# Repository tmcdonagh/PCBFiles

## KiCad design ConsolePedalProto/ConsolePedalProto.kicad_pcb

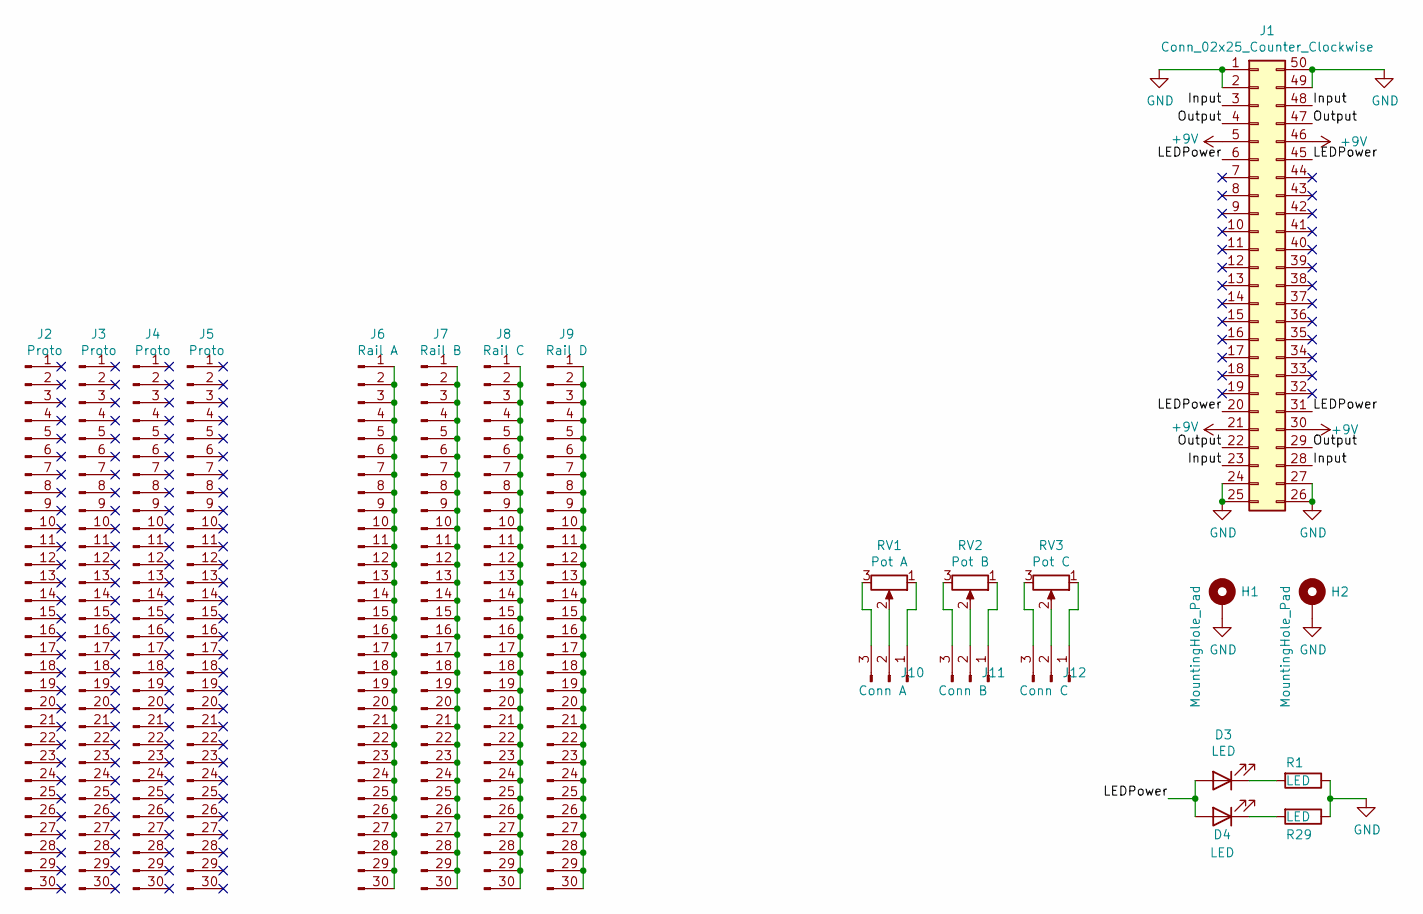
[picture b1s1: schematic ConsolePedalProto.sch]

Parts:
D3, D4: LED; LED_D5.0mm
H1, H2: MountingHole_Pad; MountingHole_2.5mm_Pad
J1: Conn_02x25_Counter_Clockwise; N64-Connector
J2, J3, J4, J5: Proto; PinSocket_1x30_P2.54mm_Vertical
J6: Rail A; Rail
J7: Rail B; Rail
J8: Rail C; Rail
J9: Rail D; Rail
J10: Conn A; PinSocket_1x03_P2.54mm_Vertical
J11: Conn B; PinSocket_1x03_P2.54mm_Vertical
J12: Conn C; PinSocket_1x03_P2.54mm_Vertical
R1, R29: LED; R_Axial_DIN0207_L6.3mm_D2.5mm_P10.16mm_Horizontal
RV1: Pot A; Potentiometer_Bourns_PTV09A-1_Single_Vertical
RV2: Pot B; Potentiometer_Bourns_PTV09A-1_Single_Vertical
RV3: Pot C; Potentiometer_Bourns_PTV09A-1_Single_Vertical

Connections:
+9V: J1.5, J1.21, J1.30, J1.46
/Input: J1.3, J1.23, J1.28, J1.48
/LEDPower: D3.2 (A), D4.2 (A), J1.6, J1.20, J1.31, J1.45
/Output: J1.4, J1.22, J1.29, J1.47
GND: H1.1, H2.1, J1.1, J1.2, J1.24, J1.25, J1.26, J1.27, J1.49, J1.50, R1.1, R29.1
unnamed: D3.1 (K), R1.2
unnamed: D4.1 (K), R29.2
unnamed: J6.1, J6.2, J6.3, J6.4, J6.5, J6.6, J6.7, J6.8, J6.9, J6.10, J6.11, J6.12, J6.13, J6.14, J6.15, J6.16, J6.17, J6.18, J6.19, J6.20, J6.21, J6.22, J6.23, J6.24, J6.25, J6.26, J6.27, J6.28, J6.29, J6.30
unnamed: J7.1, J7.2, J7.3, J7.4, J7.5, J7.6, J7.7, J7.8, J7.9, J7.10, J7.11, J7.12, J7.13, J7.14, J7.15, J7.16, J7.17, J7.18, J7.19, J7.20, J7.21, J7.22, J7.23, J7.24, J7.25, J7.26, J7.27, J7.28, J7.29, J7.30
unnamed: J8.1, J8.2, J8.3, J8.4, J8.5, J8.6, J8.7, J8.8, J8.9, J8.10, J8.11, J8.12, J8.13, J8.14, J8.15, J8.16, J8.17, J8.18, J8.19, J8.20, J8.21, J8.22, J8.23, J8.24, J8.25, J8.26, J8.27, J8.28, J8.29, J8.30
unnamed: J9.1, J9.2, J9.3, J9.4, J9.5, J9.6, J9.7, J9.8, J9.9, J9.10, J9.11, J9.12, J9.13, J9.14, J9.15, J9.16, J9.17, J9.18, J9.19, J9.20, J9.21, J9.22, J9.23, J9.24, J9.25, J9.26, J9.27, J9.28, J9.29, J9.30
unnamed: J10.1, RV1.1
unnamed: J10.2, RV1.2
unnamed: J10.3, RV1.3
unnamed: J11.1, RV2.1
unnamed: J11.2, RV2.2
unnamed: J11.3, RV2.3
unnamed: J12.1, RV3.1
unnamed: J12.2, RV3.2
unnamed: J12.3, RV3.3

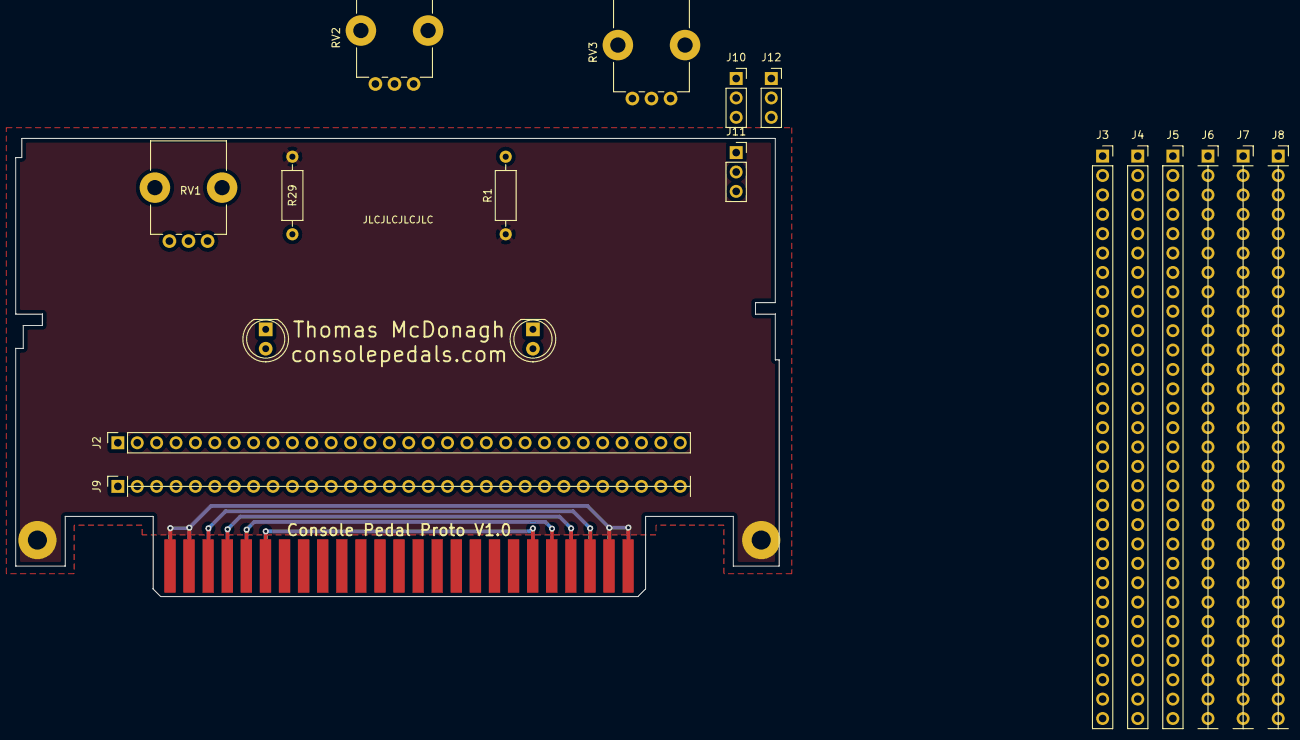
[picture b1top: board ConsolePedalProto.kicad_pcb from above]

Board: 2 copper layers, 100.0 x 60.0 mm, 21 parts (0 on the bottom side), 20 nets.

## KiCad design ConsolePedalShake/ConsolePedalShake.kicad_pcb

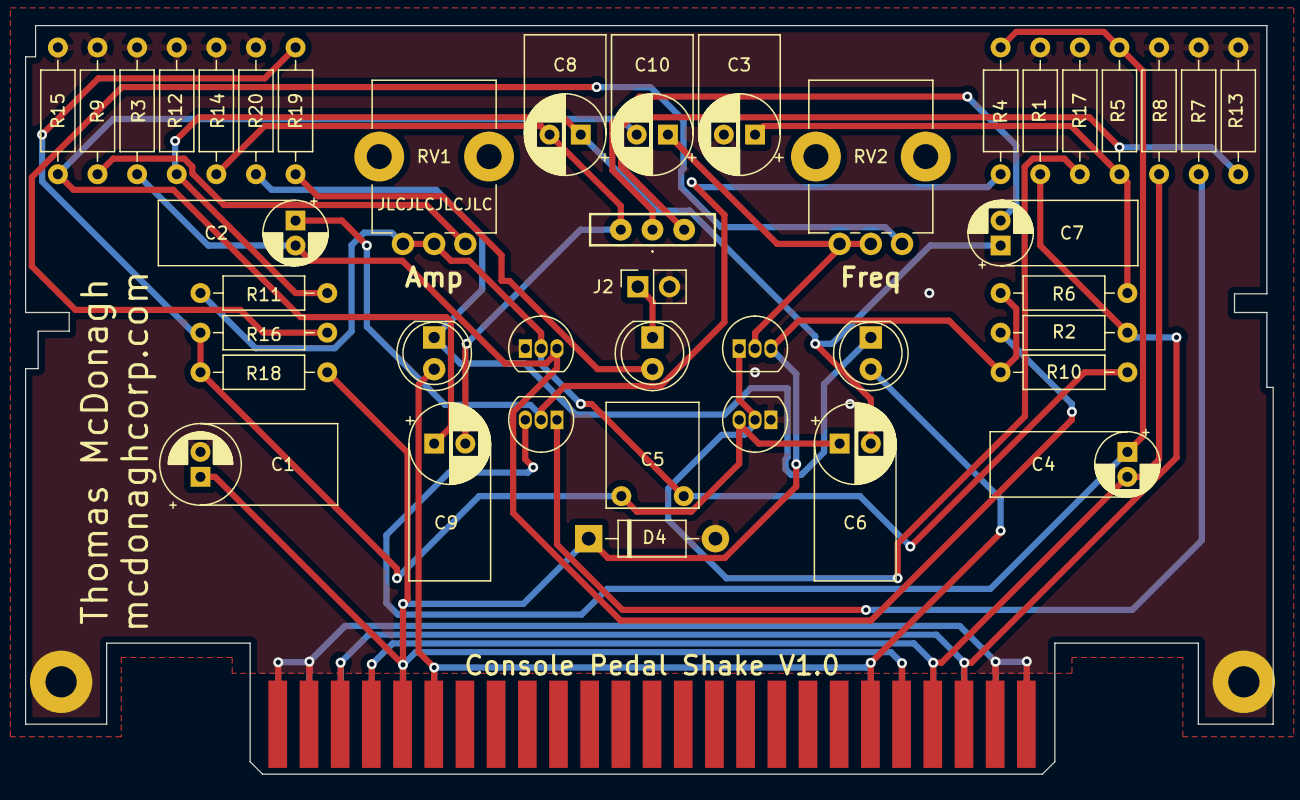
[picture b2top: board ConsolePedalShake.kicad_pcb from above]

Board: 2 copper layers, 100.0 x 60.0 mm, 45 parts (0 on the bottom side), 24 nets.

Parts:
C1: 100uF; CP_Radial_D6.3mm_P2.00mm
C2, C4, C7: 4.7uF; CP_Radial_D5.0mm_P2.00mm
C3, C8, C10: 22uF; CP_Radial_D6.3mm_P2.50mm
C5: 0.047uF; C_Flat_L7.2_H6.5
C6, C9: 10uF; CP_Radial_D6.3mm_P2.50mm
D1, D2: LED; LED_D5.0mm
D3: Pulse; LED_D5.0mm
D4: 1N4001; D_DO-41_SOD81_P10.16mm_Horizontal
H1, H2: MountingHole_Pad; MountingHole_2.5mm_Pad
J1: Conn_02x25_Counter_Clockwise; N64-Connector
J2: JP1; PinSocket_1x02_P2.54mm_Vertical
Q1, Q2, Q3, Q4: 2N5088; TO-92_Inline
R1, R8: 1M; R_Axial_DIN0207_L6.3mm_D2.5mm_P10.16mm_Horizontal
R2, R3, R11: 47K; R_Axial_DIN0207_L6.3mm_D2.5mm_P10.16mm_Horizontal
R4: 470K; R_Axial_DIN0207_L6.3mm_D2.5mm_P10.16mm_Horizontal
R5, R17: 6.8K; R_Axial_DIN0207_L6.3mm_D2.5mm_P10.16mm_Horizontal
R6, R7, R12, R14, R15, R18, R19: 2.2K; R_Axial_DIN0207_L6.3mm_D2.5mm_P10.16mm_Horizontal
R9: 15K; R_Axial_DIN0207_L6.3mm_D2.5mm_P10.16mm_Horizontal
R10: 330K; R_Axial_DIN0207_L6.3mm_D2.5mm_P10.16mm_Horizontal
R13: 220; R_Axial_DIN0207_L6.3mm_D2.5mm_P10.16mm_Horizontal
R16: 27K; R_Axial_DIN0207_L6.3mm_D2.5mm_P10.16mm_Horizontal
R20: 100K; R_Axial_DIN0207_L6.3mm_D2.5mm_P10.16mm_Horizontal
RV1: Amp; Potentiometer_Bourns_PTV09A-1_Single_Vertical
RV2: Freq; Potentiometer_Bourns_PTV09A-1_Single_Vertical
SW1: Speed; MSS10255914AD

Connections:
+9V: C1.1, D4.1, J1.5, J1.21, J1.30, J1.46, Q3.3, R6.1, R10.2, R18.2
/Input: J1.3, J1.23, J1.28, J1.48, R1.2, R2.1
/LEDPower: D1.2, D2.2, J1.6, J1.20, J1.31, J1.45
/Output: C4.2, J1.4, J1.22, J1.29, J1.47, R8.1
GND: C1.2, C3.2, D4.2, H1.1, H2.1, J1.1, J1.2, J1.24, J1.25, J1.26, J1.27, J1.49, J1.50, J2.2, Q2.1, Q4.1, R1.1, R3.2, R7.2, R8.2, R9.1, R12.2, R13.2, R14.2, R15.2, R17.1, R20.1
unnamed: C2.1, Q1.2, R4.1
unnamed: C2.2, Q2.3, R2.2, R3.1
unnamed: C3.1, R5.1, R6.2
unnamed: C4.1, Q1.3, R4.2, R5.2
unnamed: C5.1, Q2.2, R10.1, R11.1, RV1.2, RV1.3
unnamed: C5.2, C6.1, Q4.3, R16.2, R18.1, R19.2
unnamed: C6.2, C7.1, C8.1, R11.2, R12.1
unnamed: C7.2, SW1.1
unnamed: C8.2, C9.2, R14.1, SW1.2
unnamed: C10.1, Q3.2, RV2.2, RV2.3
unnamed: C9.1, C10.2, R15.1
unnamed: D1.1, D2.1, R20.2
unnamed: D3.1, J2.1
unnamed: D3.2, R19.1
unnamed: Q1.1, R7.1
unnamed: Q3.1, Q4.2, R17.2
unnamed: R9.2, RV1.1
unnamed: R13.1, SW1.3
unnamed: R16.1, RV2.1

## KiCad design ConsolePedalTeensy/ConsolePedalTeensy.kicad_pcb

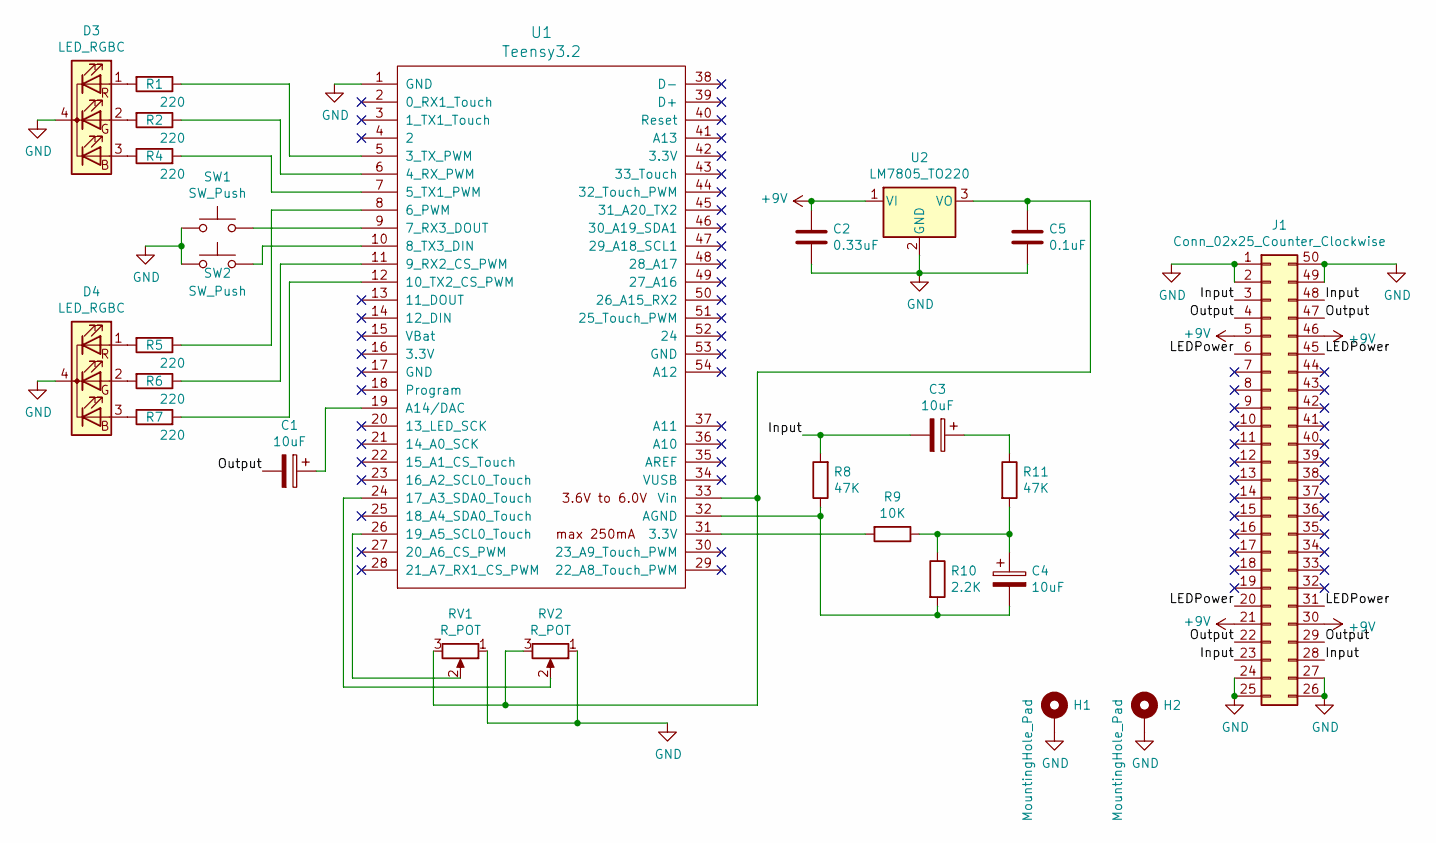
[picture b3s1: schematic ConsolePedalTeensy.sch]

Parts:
C1, C3, C4: 10uF; CP_Axial_L10.0mm_D6.0mm_P15.00mm_Horizontal
C2: 0.33uF; C_Flat_L7.2_H6.5
C5: 0.1uF; C_Flat_L7.2_H6.5
D3, D4: LED_RGBC; LED_D5.0mm-4_RGB_Wide_Pins
H1, H2: MountingHole_Pad; MountingHole_2.5mm_Pad
J1: Conn_02x25_Counter_Clockwise; N64-Connector
R1, R2, R4, R5, R6, R7: 220; R_Axial_DIN0207_L6.3mm_D2.5mm_P10.16mm_Horizontal
R8, R11: 47K; R_Axial_DIN0207_L6.3mm_D2.5mm_P10.16mm_Horizontal
R9: 10K; R_Axial_DIN0207_L6.3mm_D2.5mm_P10.16mm_Horizontal
R10: 2.2K; R_Axial_DIN0207_L6.3mm_D2.5mm_P10.16mm_Horizontal
RV1, RV2: R_POT; Potentiometer_Bourns_PTV09A-1_Single_Vertical
SW1, SW2: SW_Push; SW_PUSH_6mm
U1: Teensy3.2
U2: LM7805_TO220; TO-220-3_Horizontal_TabDown

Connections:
+9V: C2.1, J1.5, J1.21, J1.30, J1.46, U2.1 (VI)
/Input: C3.2, J1.3, J1.23, J1.28, J1.48, R8.2
/LEDPower: J1.6, J1.20, J1.31, J1.45
/Output: C1.2, J1.4, J1.22, J1.29, J1.47
GND: C2.2, C5.2, D3.4 (K), D4.4 (K), H1.1, H2.1, J1.1, J1.2, J1.24, J1.25, J1.26, J1.27, J1.49, J1.50, RV1.1, RV2.1, SW1.1, SW2.1, U1.1 (GND), U2.2 (GND)
unnamed: C1.1, U1.19 (A14/DAC)
unnamed: C3.1, R11.1
unnamed: C4.1, R9.1, R10.1, R11.2
unnamed: C4.2, R8.1, R10.2, U1.32 (AGND)
unnamed: C5.1, RV1.3, RV2.3, U1.33 (Vin), U2.3 (VO)
unnamed: D3.1 (RA), R1.2
unnamed: D3.2 (GA), R2.2
unnamed: D3.3 (BA), R4.1
unnamed: D4.1 (RA), R5.2
unnamed: D4.2 (GA), R6.2
unnamed: D4.3 (BA), R7.1
unnamed: R1.1, U1.5 (3_TX_PWM)
unnamed: R2.1, U1.6 (4_RX_PWM)
unnamed: R4.2, U1.7 (5_TX1_PWM)
unnamed: R5.1, U1.8 (6_PWM)
unnamed: R6.1, U1.11 (9_RX2_CS_PWM)
unnamed: R7.2, U1.12 (10_TX2_CS_PWM)
unnamed: R9.2, U1.31 (3.3V)
unnamed: RV1.2, U1.26 (19_A5_SCL0_Touch)
unnamed: RV2.2, U1.24 (17_A3_SDA0_Touch)
unnamed: SW1.2, U1.9 (7_RX3_DOUT)
unnamed: SW2.2, U1.10 (8_TX3_DIN)

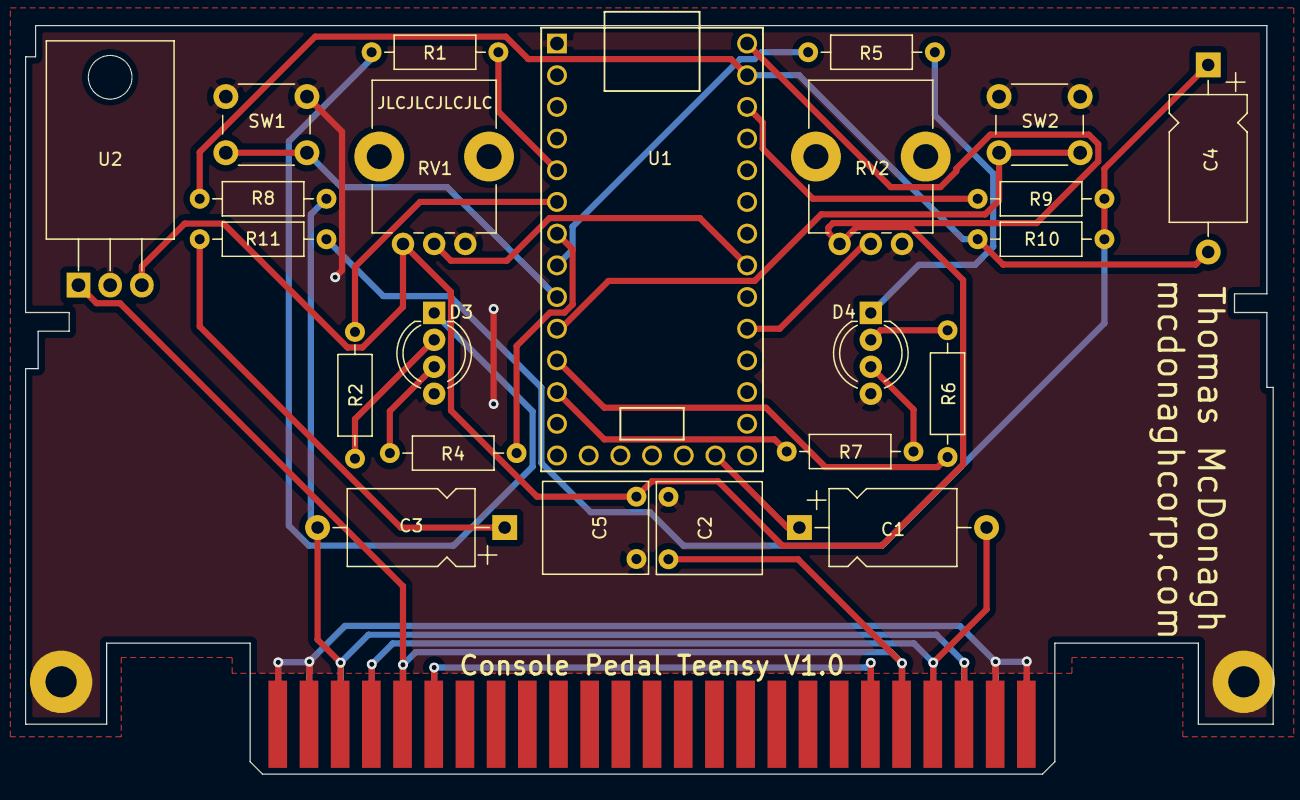
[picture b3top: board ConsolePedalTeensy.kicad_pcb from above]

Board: 2 copper layers, 100.0 x 60.0 mm, 26 parts (0 on the bottom side), 27 nets.

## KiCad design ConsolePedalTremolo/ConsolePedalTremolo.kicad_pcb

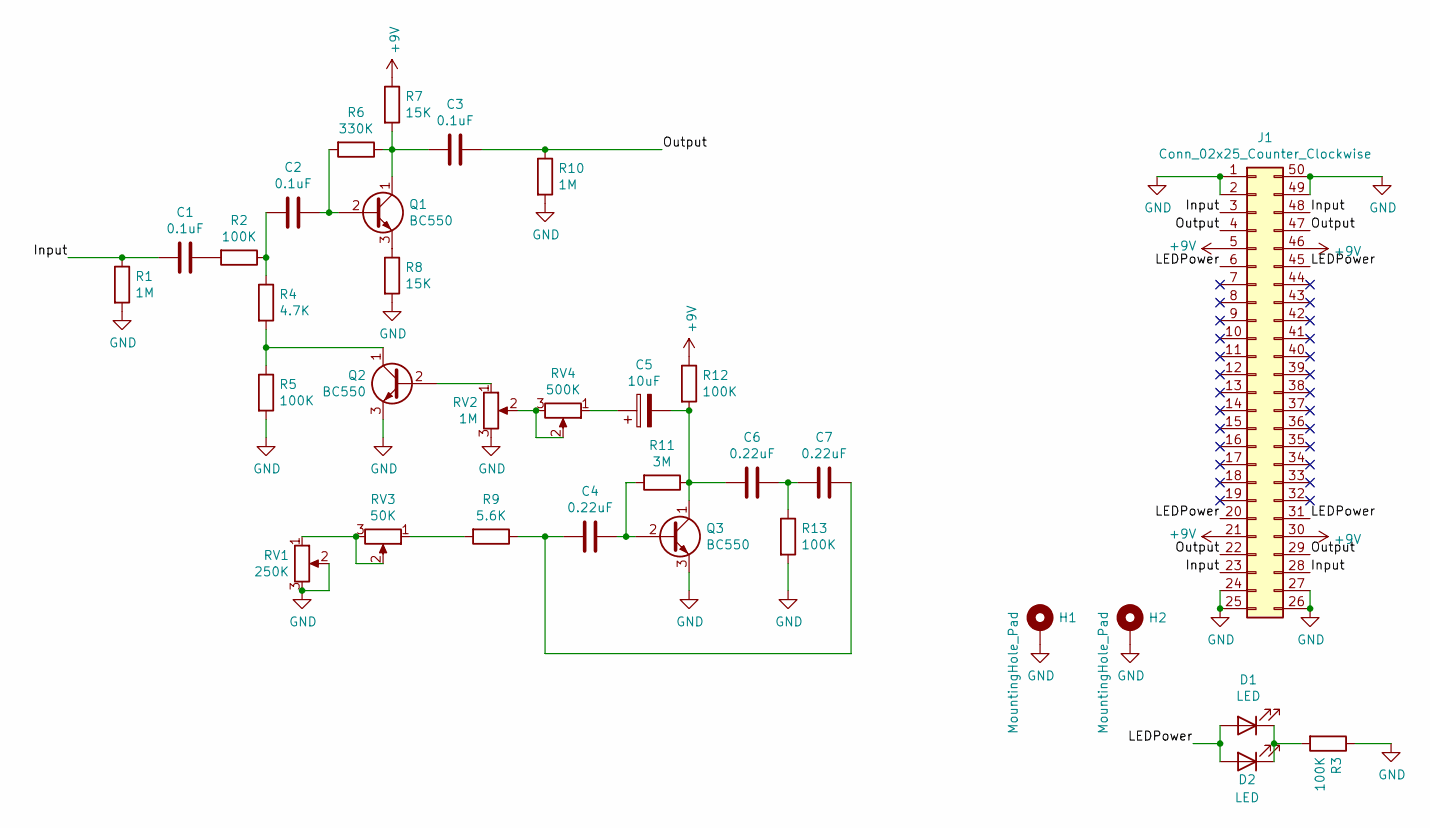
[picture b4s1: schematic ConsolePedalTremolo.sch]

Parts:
C1, C2, C3: 0.1uF; C_Flat_L7.2_H6.5
C4, C6, C7: 0.22uF; C_Flat_L7.2_H6.5
C5: 10uF; CP_Axial_L11.0mm_D6.0mm_P18.00mm_Horizontal
D1, D2: LED; LED_D5.0mm
H1, H2: MountingHole_Pad; MountingHole_2.5mm_Pad
J1: Conn_02x25_Counter_Clockwise; N64-Connector
Q1, Q2, Q3: BC550; TO-92_Inline
R1, R10: 1M; R_Axial_DIN0207_L6.3mm_D2.5mm_P10.16mm_Horizontal
R2, R3, R5, R12, R13: 100K; R_Axial_DIN0207_L6.3mm_D2.5mm_P10.16mm_Horizontal
R4: 4.7K; R_Axial_DIN0207_L6.3mm_D2.5mm_P10.16mm_Horizontal
R6: 330K; R_Axial_DIN0207_L6.3mm_D2.5mm_P10.16mm_Horizontal
R7, R8: 15K; R_Axial_DIN0207_L6.3mm_D2.5mm_P10.16mm_Horizontal
R9: 5.6K; R_Axial_DIN0207_L6.3mm_D2.5mm_P10.16mm_Horizontal
R11: 3M; R_Axial_DIN0207_L6.3mm_D2.5mm_P10.16mm_Horizontal
RV1: 250K; Potentiometer_Bourns_PTV09A-1_Single_Vertical
RV2: 1M; Potentiometer_Bourns_PTV09A-1_Single_Vertical
RV3: 50K; Potentiometer_Bourns_3386F_Vertical
RV4: 500K; Potentiometer_Bourns_3386F_Vertical

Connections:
+9V: J1.5, J1.21, J1.30, J1.46, R7.1, R12.1
/Input: C1.2, J1.3, J1.23, J1.28, J1.48, R1.1
/LEDPower: D1.2 (A), D2.2 (A), J1.6, J1.20, J1.31, J1.45
/Output: C3.2, J1.4, J1.22, J1.29, J1.47, R10.1
GND: H1.1, H2.1, J1.1, J1.2, J1.24, J1.25, J1.26, J1.27, J1.49, J1.50, Q2.3 (E), Q3.3 (E), R1.2, R3.1, R5.2, R8.2, R10.2, R13.2, RV1.2, RV1.3, RV2.3
unnamed: C1.1, R2.2
unnamed: C2.1, Q1.2 (B), R6.2
unnamed: C2.2, R2.1, R4.1
unnamed: C3.1, Q1.1 (C), R6.1, R7.2
unnamed: C4.1, Q3.2 (B), R11.2
unnamed: C4.2, C7.1, R9.1
unnamed: C5.1, RV4.1
unnamed: C5.2, C6.2, Q3.1 (C), R11.1, R12.2
unnamed: C6.1, C7.2, R13.1
unnamed: D1.1 (K), D2.1 (K), R3.2
unnamed: Q1.3 (E), R8.1
unnamed: Q2.1 (C), R4.2, R5.1
unnamed: Q2.2 (B), RV2.1
unnamed: R9.2, RV3.1
unnamed: RV1.1, RV3.2, RV3.3
unnamed: RV2.2, RV4.2, RV4.3

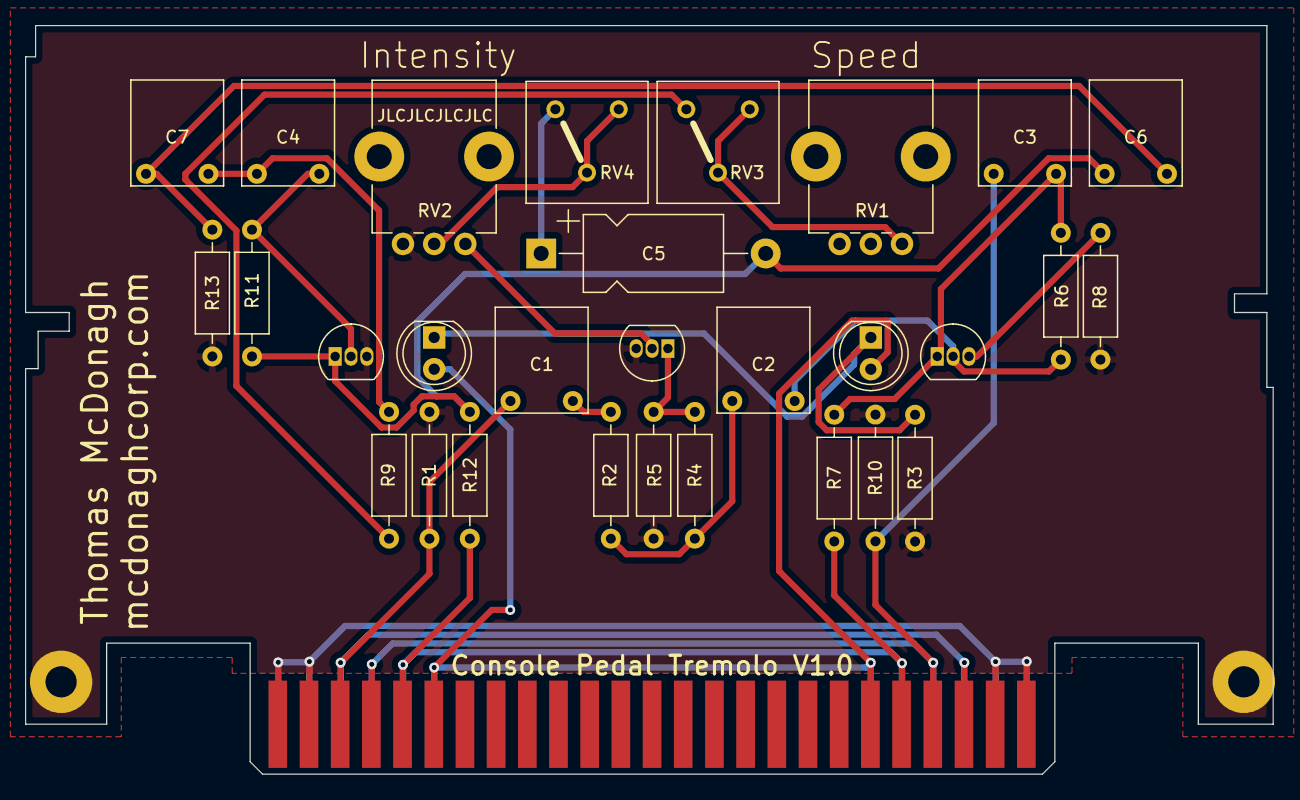
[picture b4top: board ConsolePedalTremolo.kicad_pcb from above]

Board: 2 copper layers, 100.0 x 60.0 mm, 32 parts (0 on the bottom side), 21 nets.

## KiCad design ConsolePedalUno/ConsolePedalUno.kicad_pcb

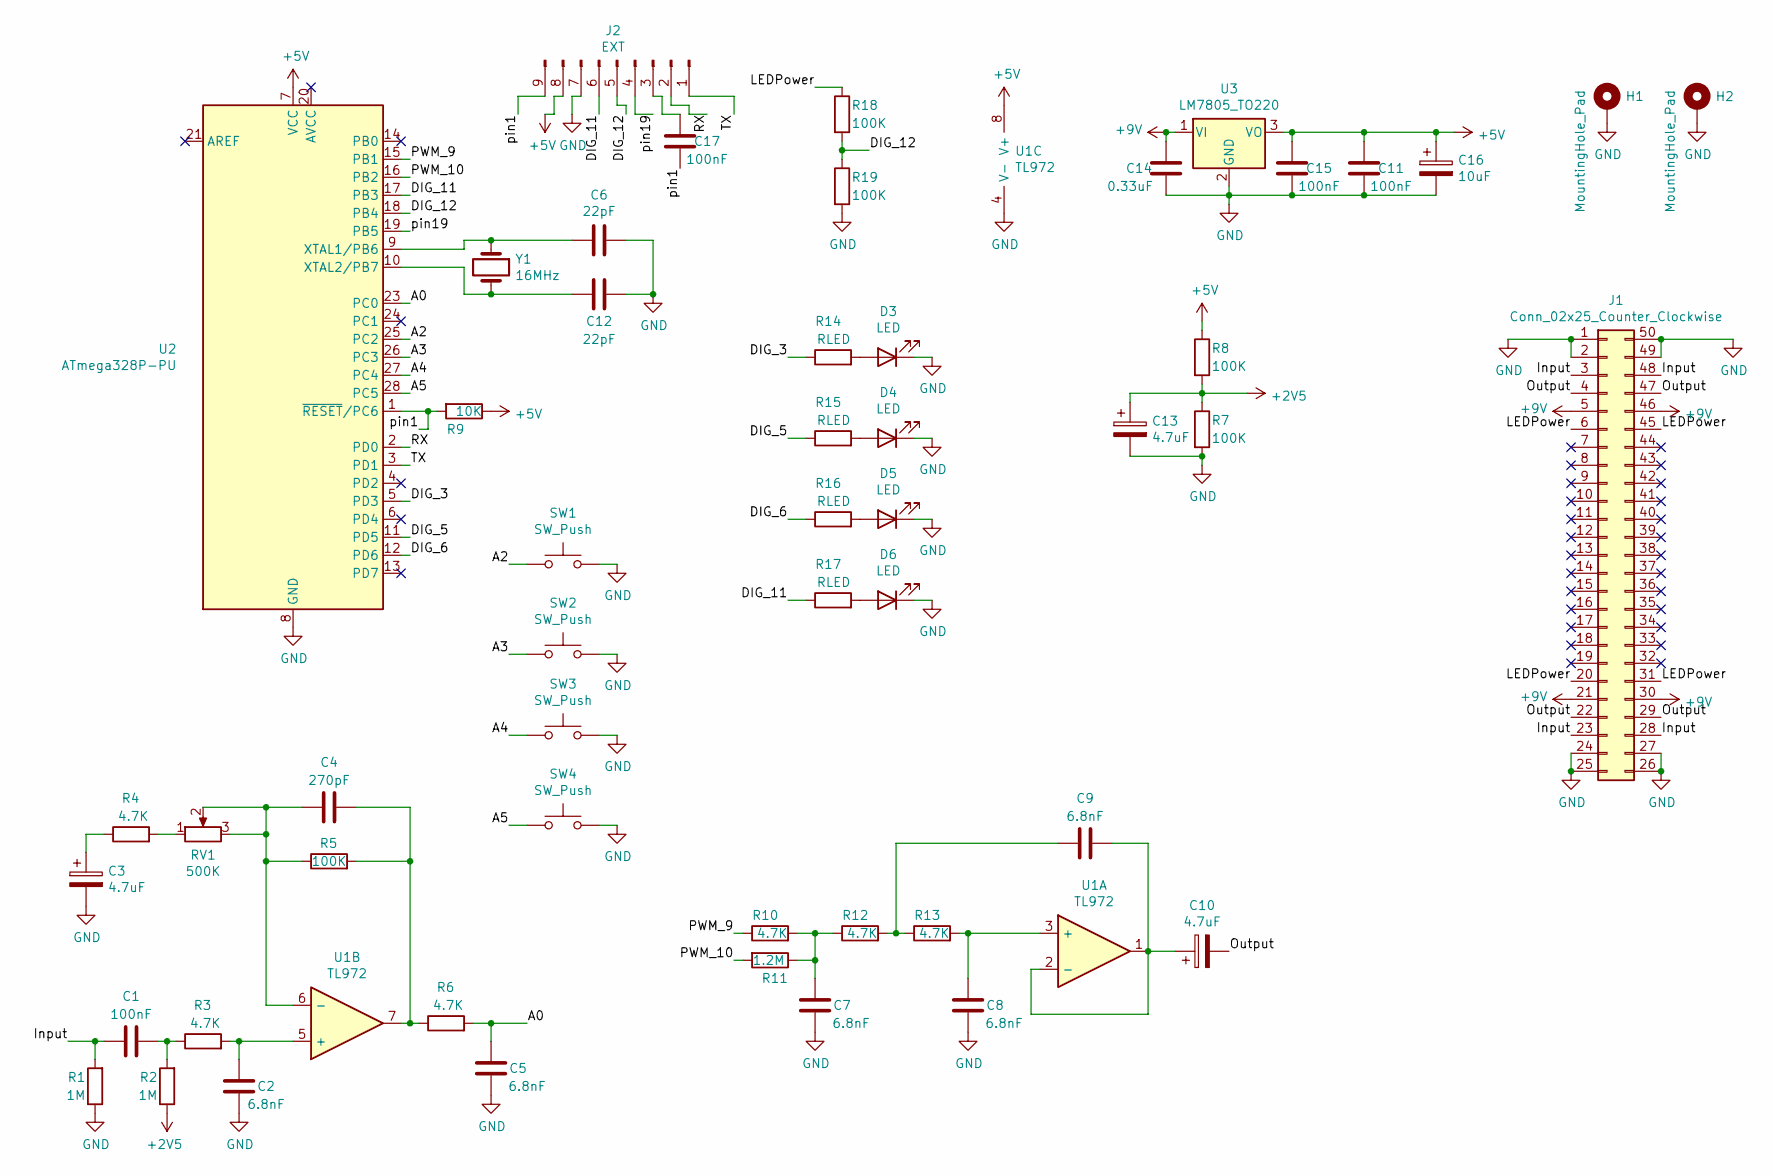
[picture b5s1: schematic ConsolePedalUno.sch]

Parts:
C1, C11, C15, C17: 100nF; C_Flat_L7.2_H6.5
C2, C5, C7, C8, C9: 6.8nF; C_Flat_L7.2_H6.5
C3, C10, C13: 4.7uF; CP_Radial_D5.0mm_P2.00mm_L11.0mm
C4: 270pF; C_Axial_L3.8mm_D2.6mm_P7.50mm_Horizontal
C6, C12: 22pF; C_Axial_L3.8mm_D2.6mm_P7.50mm_Horizontal
C14: 0.33uF; C_Flat_L7.2_H6.5
C16: 10uF; CP_Radial_D6.3mm_P2.50mm_L7.0mm
D3, D4, D5, D6: LED; LED_D5.0mm
H1, H2: MountingHole_Pad; MountingHole_2.5mm_Pad
J1: Conn_02x25_Counter_Clockwise; N64-Connector
J2: EXT; PinSocket_1x09_P2.54mm_Vertical
R1, R2: 1M; R_Axial_DIN0207_L6.3mm_D2.5mm_P10.16mm_Horizontal
R3, R4, R6, R10, R12, R13: 4.7K; R_Axial_DIN0207_L6.3mm_D2.5mm_P10.16mm_Horizontal
R5, R7, R8, R18, R19: 100K; R_Axial_DIN0207_L6.3mm_D2.5mm_P10.16mm_Horizontal
R9: 10K; R_Axial_DIN0207_L6.3mm_D2.5mm_P10.16mm_Horizontal
R11: 1.2M; R_Axial_DIN0207_L6.3mm_D2.5mm_P10.16mm_Horizontal
R14, R15, R16, R17: RLED; R_Axial_DIN0207_L6.3mm_D2.5mm_P10.16mm_Horizontal
RV1: 500K; Potentiometer_Bourns_3386F_Vertical
SW1, SW2, SW3, SW4: SW_Push; SW_PUSH_6mm
U1: TL972; DIP-8_W7.62mm_Socket
U2: ATmega328P-PU; DIP-28_W7.62mm
U3: LM7805_TO220; TO-220-3_Horizontal_TabDown
Y1: 16MHz; Crystal_HC49-U_Vertical

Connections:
+2V5: C13.1, R2.1, R7.1, R8.2
+5V: C11.1, C15.1, C16.1, J2.8, R8.1, R9.1, U1.8 (V+), U2.7 (VCC), U3.3 (VO)
+9V: C14.1, J1.5, J1.21, J1.30, J1.46, U3.1 (VI)
/A0: C5.1, R6.2, U2.23 (PC0)
/A2: SW1.1, U2.25 (PC2)
/A3: SW2.1, U2.26 (PC3)
/A4: SW3.1, U2.27 (PC4)
/A5: SW4.1, U2.28 (PC5)
/DIG_3: R14.1, U2.5 (PD3)
/DIG_5: R15.1, U2.11 (PD5)
/DIG_6: R16.1, U2.12 (PD6)
/DIG_11: J2.6, R17.1, U2.17 (PB3)
/DIG_12: J2.5, R18.2, R19.1, U2.18 (PB4)
/Input: C1.1, J1.3, J1.23, J1.28, J1.48, R1.2
/LEDPower: J1.6, J1.20, J1.31, J1.45, R18.1
/Output: C10.2, J1.4, J1.22, J1.29, J1.47
/PWM_9: R10.1, U2.15 (PB1)
/PWM_10: R11.2, U2.16 (PB2)
/RX: J2.2, U2.2 (PD0)
/TX: J2.1, U2.3 (PD1)
/pin1: C17.1, J2.9, R9.2, U2.1 (~RESET~/PC6)
/pin19: J2.4, U2.19 (PB5)
GND: C2.2, C3.2, C5.2, C6.1, C7.2, C8.2, C11.2, C12.2, C13.2, C14.2, C15.2, C16.2, D3.1 (K), D4.1 (K), D5.1 (K), D6.1 (K), H1.1, H2.1, J1.1, J1.2, J1.24, J1.25, J1.26, J1.27, J1.49, J1.50, J2.7, R1.1, R7.2, R19.2, SW1.2, SW2.2, SW3.2, SW4.2, U1.4 (V-), U2.8 (GND), U2.22 (GND), U3.2 (GND)
unnamed: C1.2, R2.2, R3.1
unnamed: C2.1, R3.2, U1.5 (+)
unnamed: C3.1, R4.1
unnamed: C4.1, R5.1, RV1.2, RV1.3, U1.6 (-)
unnamed: C4.2, R5.2, R6.1, U1.7
unnamed: C6.2, U2.9 (XTAL1/PB6), Y1.1
unnamed: C7.1, R10.2, R11.1, R12.1
unnamed: C8.1, R13.2, U1.3 (+)
unnamed: C9.1, R12.2, R13.1
unnamed: C9.2, C10.1, U1.1, U1.2 (-)
unnamed: C12.1, U2.10 (XTAL2/PB7), Y1.2
unnamed: C17.2, J2.3
unnamed: D3.2 (A), R14.2
unnamed: D4.2 (A), R15.2
unnamed: D5.2 (A), R16.2
unnamed: D6.2 (A), R17.2
unnamed: R4.2, RV1.1

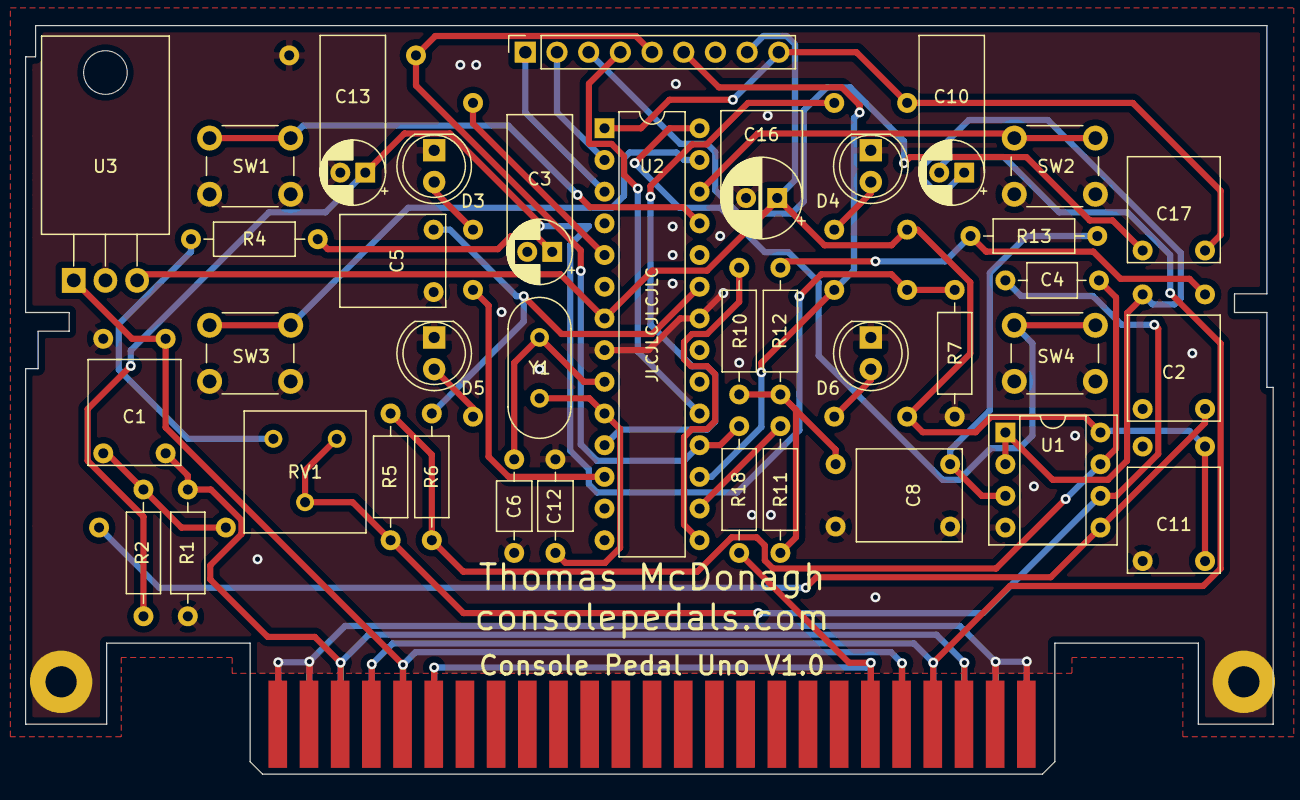
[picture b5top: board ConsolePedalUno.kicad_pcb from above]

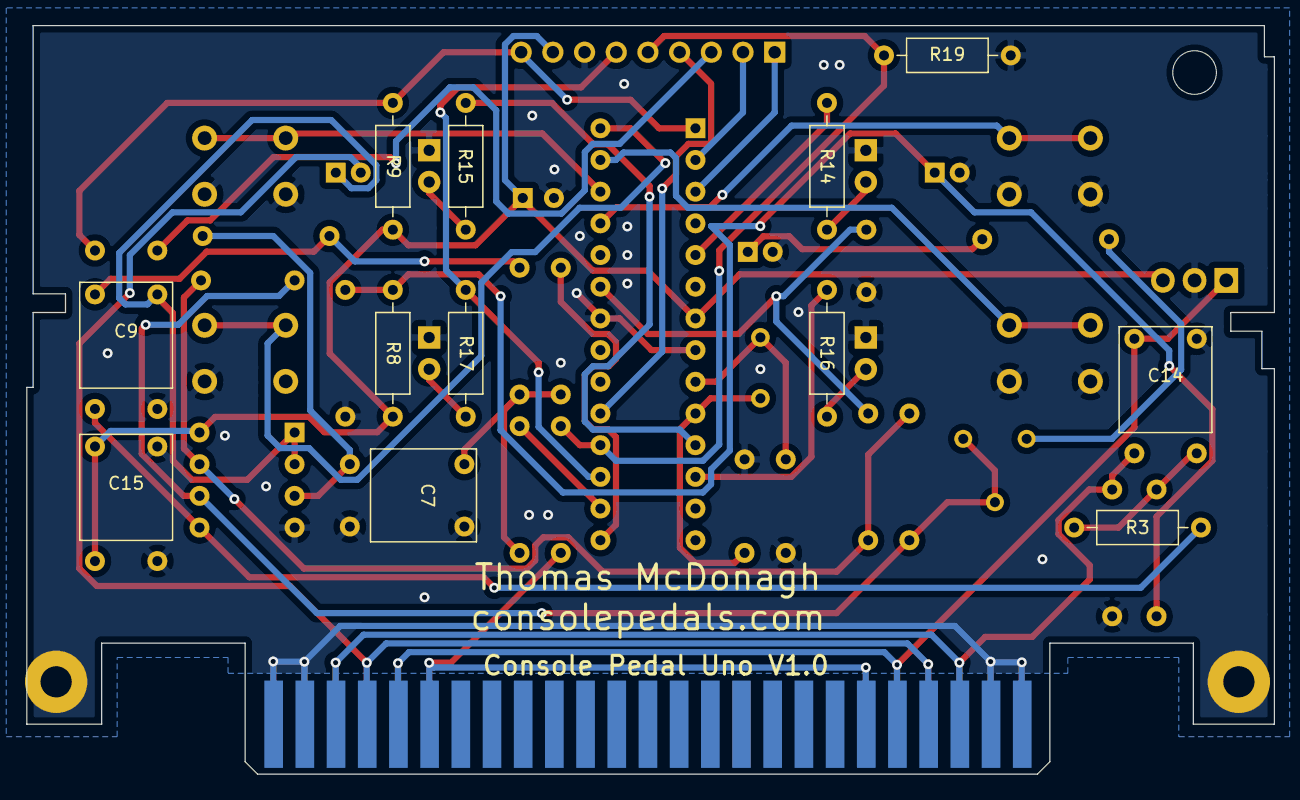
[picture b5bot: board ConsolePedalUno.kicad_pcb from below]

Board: 2 copper layers, 100.0 x 60.0 mm, 53 parts (12 on the bottom side), 40 nets.

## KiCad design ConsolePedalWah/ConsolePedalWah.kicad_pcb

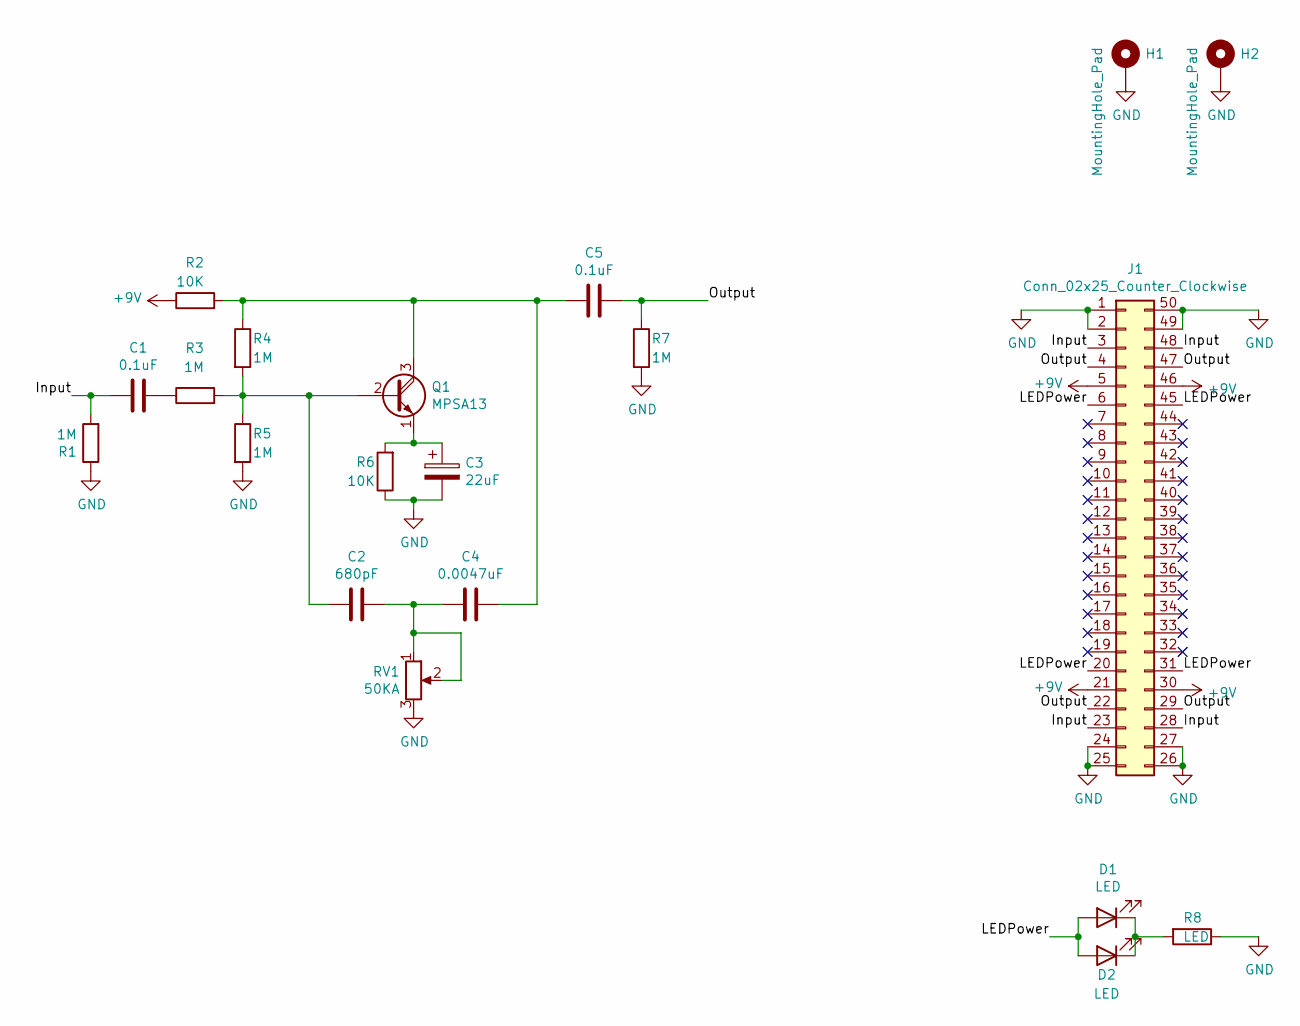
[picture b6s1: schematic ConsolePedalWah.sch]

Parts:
C1, C5: 0.1uF; C_Flat_L7.2_H6.5
C2: 680pF; C_Axial_L3.8mm_D2.6mm_P7.50mm_Horizontal
C3: 22uF; CP_Radial_D6.3mm_P2.50mm
C4: 0.0047uF; C_Flat_L7.2_H6.5
D1, D2: LED; LED_D5.0mm
H1, H2: MountingHole_Pad; MountingHole_2.5mm_Pad
J1: Conn_02x25_Counter_Clockwise; N64-Connector
Q1: MPSA13; TO-92_Inline
R1, R3, R4, R5, R7: 1M; R_Axial_DIN0207_L6.3mm_D2.5mm_P10.16mm_Horizontal
R2, R6: 10K; R_Axial_DIN0207_L6.3mm_D2.5mm_P10.16mm_Horizontal
R8: LED; R_Axial_DIN0207_L6.3mm_D2.5mm_P10.16mm_Horizontal
RV1: 50KA; Potentiometer_Bourns_PTV09A-1_Single_Vertical

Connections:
+9V: J1.5, J1.21, J1.30, J1.46, R2.1
/Input: C1.2, J1.3, J1.23, J1.28, J1.48, R1.2
/LEDPower: D1.2 (A), D2.2 (A), J1.6, J1.20, J1.31, J1.45
/Output: C5.1, J1.4, J1.22, J1.29, J1.47, R7.1
GND: C3.2, H1.1, H2.1, J1.1, J1.2, J1.24, J1.25, J1.26, J1.27, J1.49, J1.50, R1.1, R5.2, R6.1, R7.2, R8.1, RV1.3
unnamed: C1.1, R3.1
unnamed: C2.1, Q1.2 (B), R3.2, R4.2, R5.1
unnamed: C2.2, C4.1, RV1.1, RV1.2
unnamed: C3.1, Q1.1 (E), R6.2
unnamed: C4.2, C5.2, Q1.3 (C), R2.2, R4.1
unnamed: D1.1 (K), D2.1 (K), R8.2

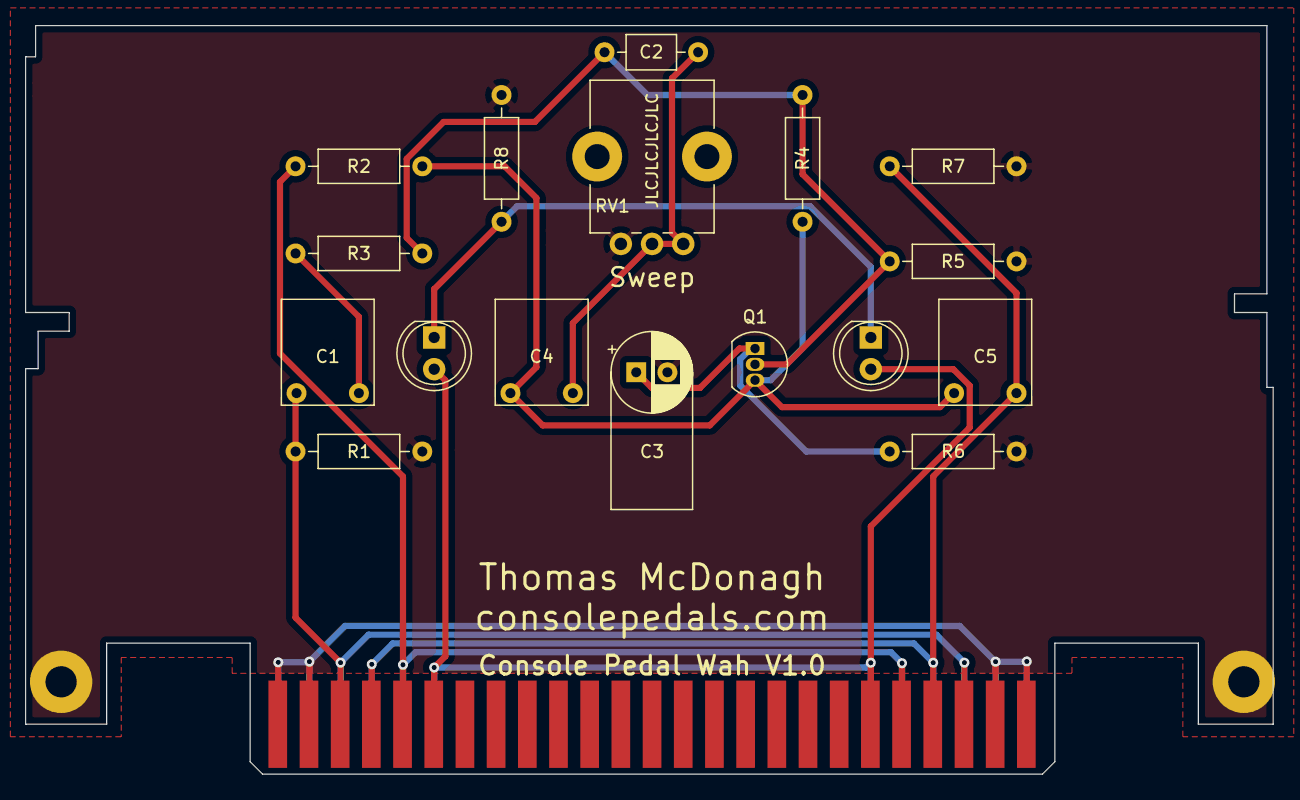
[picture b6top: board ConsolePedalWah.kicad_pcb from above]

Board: 2 copper layers, 100.0 x 60.0 mm, 20 parts (0 on the bottom side), 11 nets.
